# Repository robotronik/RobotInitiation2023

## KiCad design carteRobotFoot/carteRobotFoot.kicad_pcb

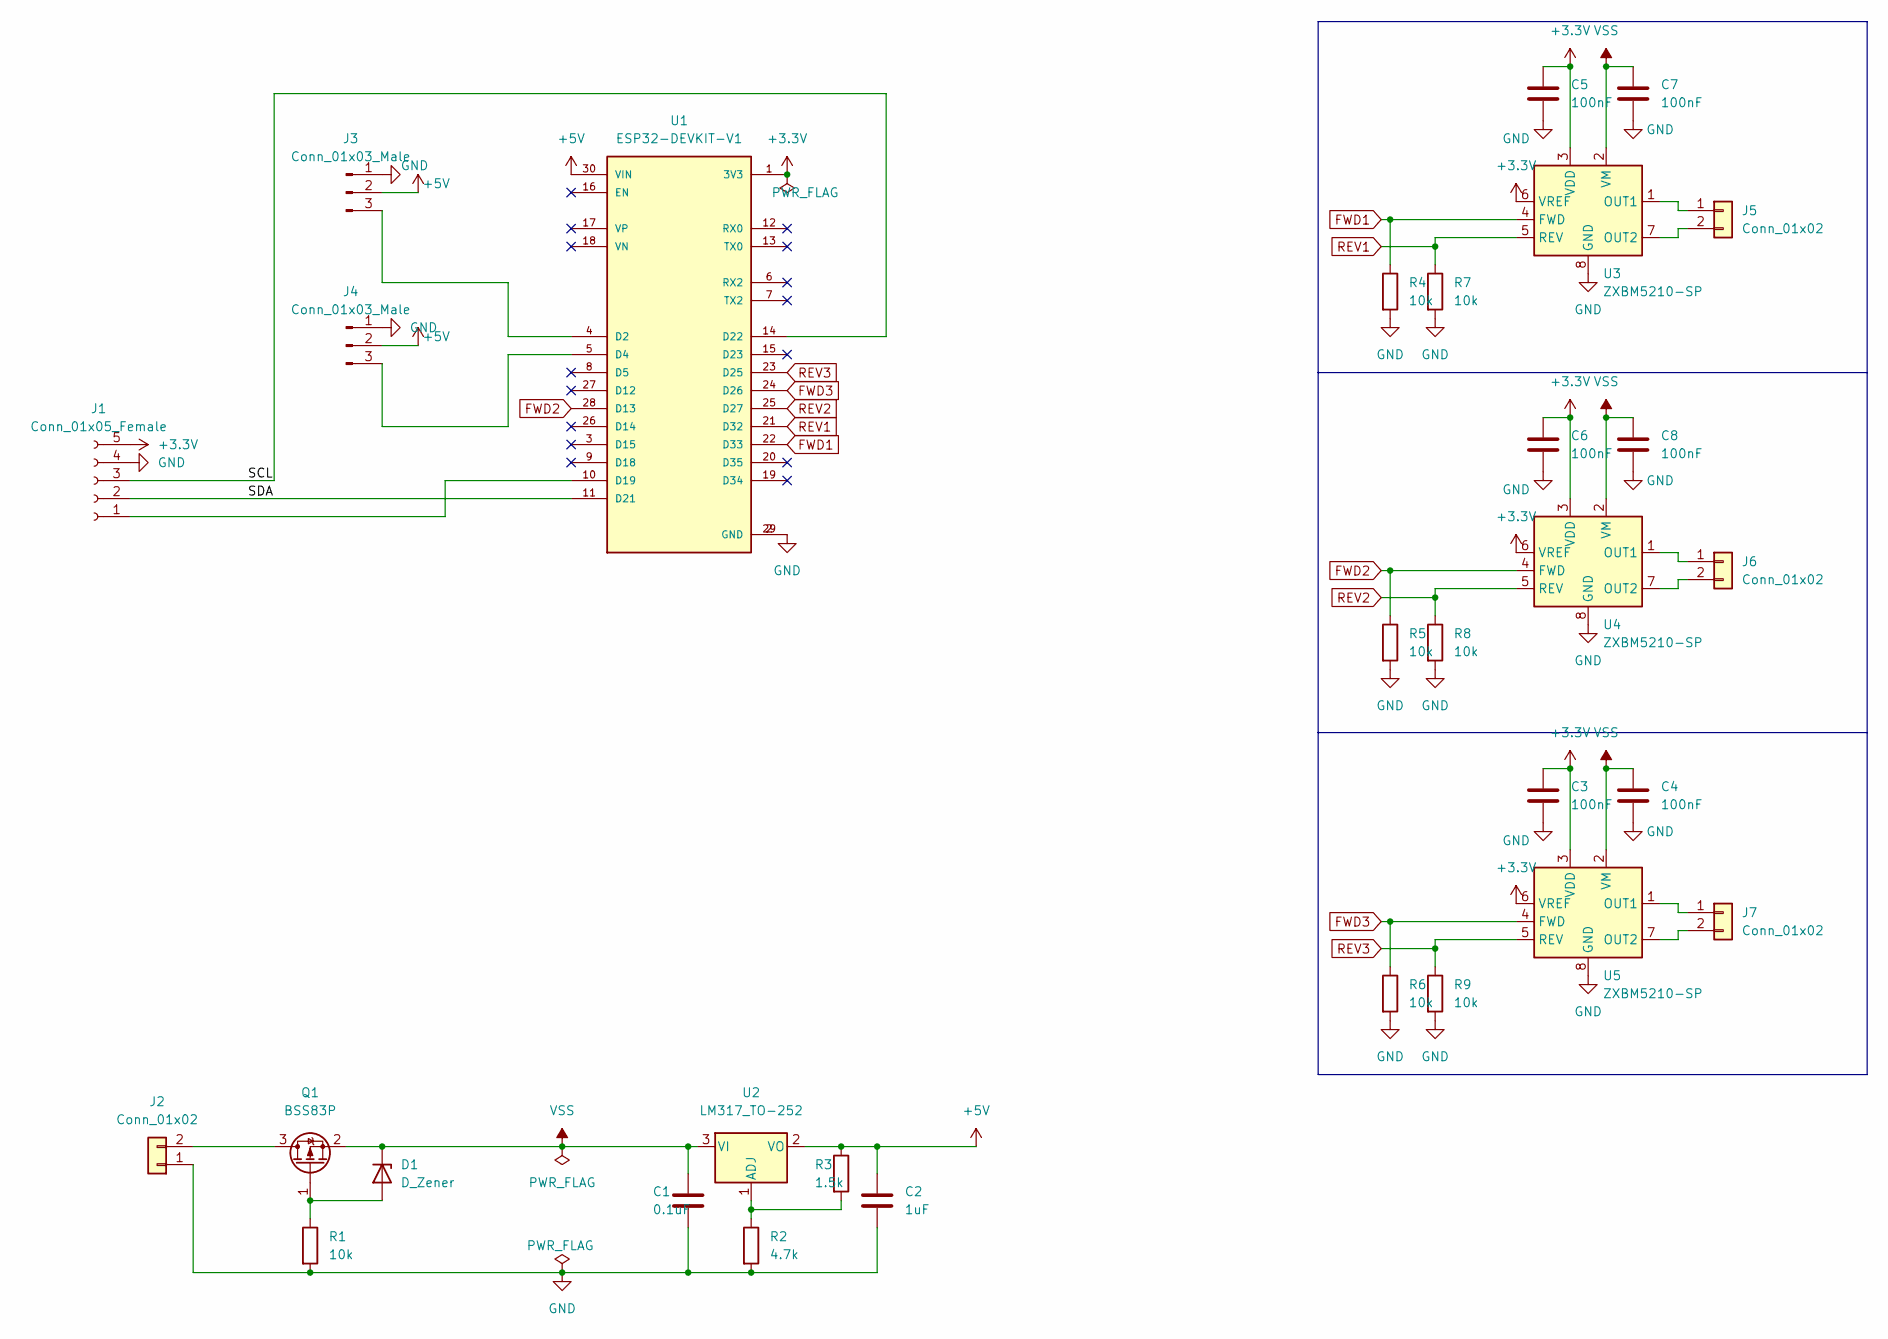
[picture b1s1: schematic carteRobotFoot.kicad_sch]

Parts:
C1: 0.1uF; C_0805_2012Metric
C2: 1uF; C_0805_2012Metric
C3, C4, C5, C6, C7, C8: 100nF; C_0805_2012Metric
D1: D_Zener; D_SOD-123
J1: Conn_01x05_Female; PinHeader_1x05_P2.54mm_Vertical
J2: Conn_01x02; TerminalBlock_bornier-2_P5.08mm
J3, J4: Conn_01x03_Male; PinHeader_1x03_P2.54mm_Vertical
J5, J6, J7: Conn_01x02; JST_XH_B2B-XH-A_1x02_P2.50mm_Vertical
Q1: BSS83P; SOT-23
R1, R4, R5, R6, R7, R8, R9: 10k; R_0805_2012Metric
R2: 4.7k; R_0805_2012Metric
R3: 1.5k; R_0805_2012Metric
U1: ESP32-DEVKIT-V1; MODULE_ESP32_DEVKIT_V1; PARTREV N/A
U2: LM317_TO-252; TO-252-2
U3, U4, U5: ZXBM5210-SP; Diodes_SO-8EP

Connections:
+3.3V: C3.1, C5.1, C6.1, J1.5, U1.1 (3V3), U3.3 (VDD), U3.6 (VREF), U4.3 (VDD), U4.6 (VREF), U5.3 (VDD), U5.6 (VREF)
+5V: C2.1, J3.2, J4.2, R3.1, U1.30 (VIN), U2.2 (VO)
/SCL: J1.3, U1.14 (D22)
/SDA: J1.2, U1.11 (D21)
FWD1: R4.1, U1.22 (D33), U3.4 (FWD)
FWD2: R5.1, U1.28 (D13), U4.4 (FWD)
FWD3: R6.1, U1.24 (D26), U5.4 (FWD)
GND: C1.2, C2.2, C3.2, C4.2, C5.2, C6.2, C7.2, C8.2, J1.4, J2.1, J3.1, J4.1, R1.2, R2.2, R4.2, R5.2, R6.2, R7.2, R8.2, R9.2, U1.2 (GND), U1.29 (GND), U3.8 (GND), U3.9 (GND), U4.8 (GND), U4.9 (GND), U5.8 (GND), U5.9 (GND)
unnamed: D1.2 (A), Q1.1 (G), R1.1
unnamed: J1.1, U1.10 (D19)
unnamed: J2.2, Q1.3 (D)
unnamed: J3.3, U1.4 (D2)
unnamed: J4.3, U1.5 (D4)
unnamed: J5.1, U3.1 (OUT1)
unnamed: J5.2, U3.7 (OUT2)
unnamed: J6.1, U4.1 (OUT1)
unnamed: J6.2, U4.7 (OUT2)
unnamed: J7.1, U5.1 (OUT1)
unnamed: J7.2, U5.7 (OUT2)
unnamed: R2.1, R3.2, U2.1 (ADJ)
REV1: R7.1, U1.21 (D32), U3.5 (REV)
REV2: R8.1, U1.25 (D27), U4.5 (REV)
REV3: R9.1, U1.23 (D25), U5.5 (REV)
VSS: C1.1, C4.1, C7.1, C8.1, D1.1 (K), Q1.2 (S), U2.3 (VI), U3.2 (VM), U4.2 (VM), U5.2 (VM)

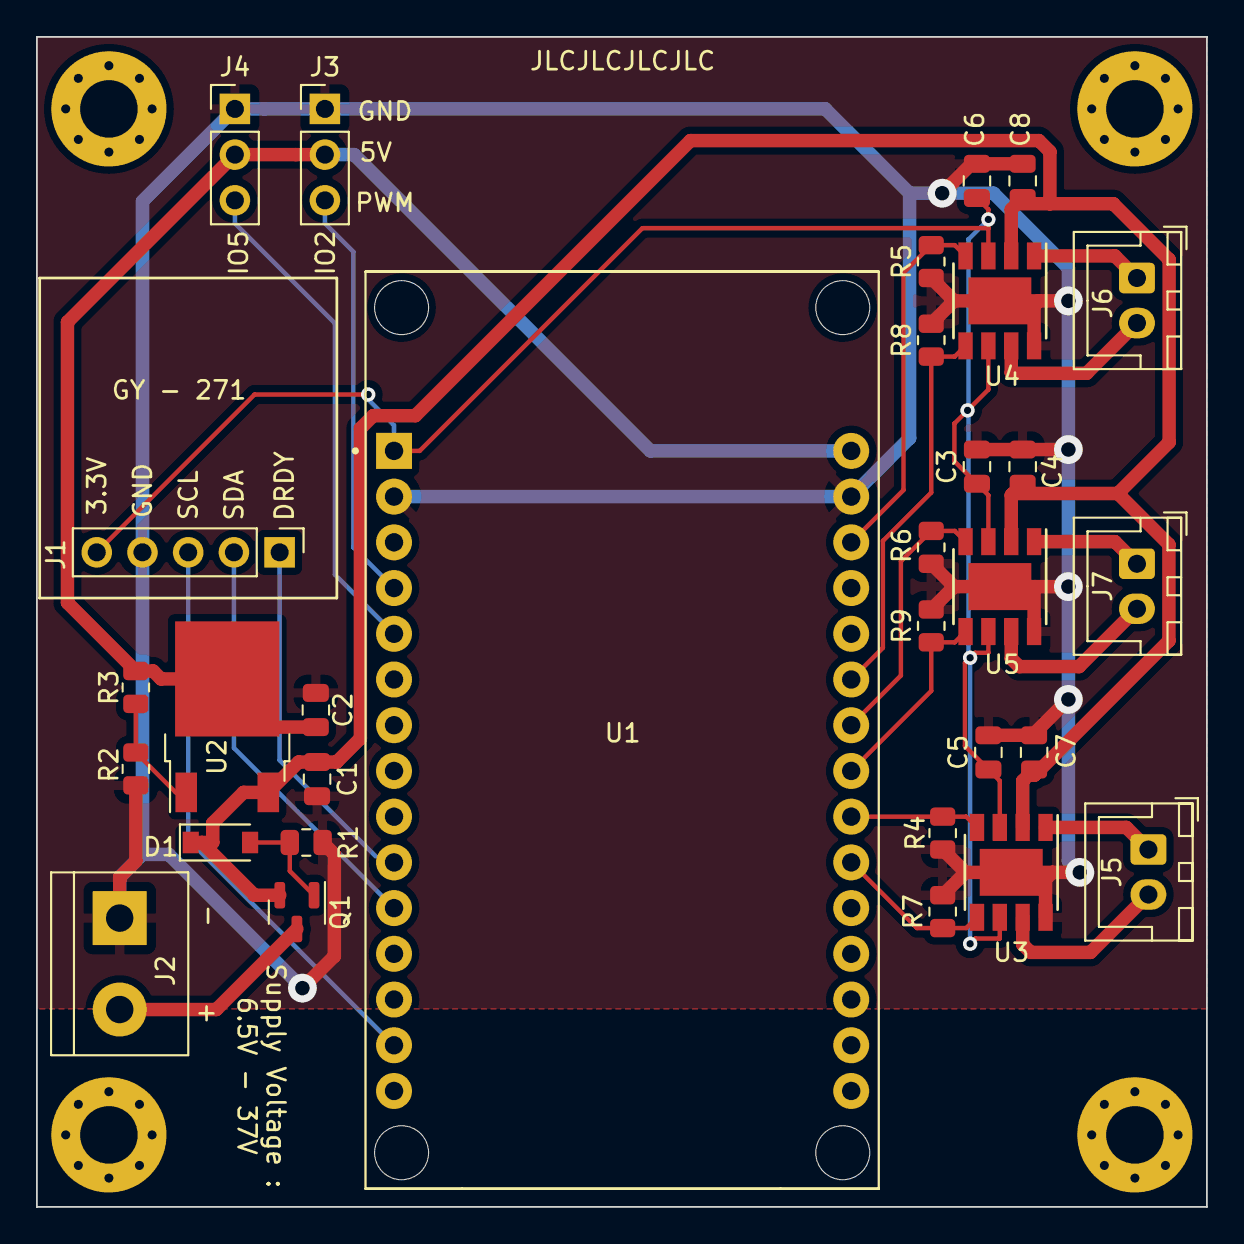
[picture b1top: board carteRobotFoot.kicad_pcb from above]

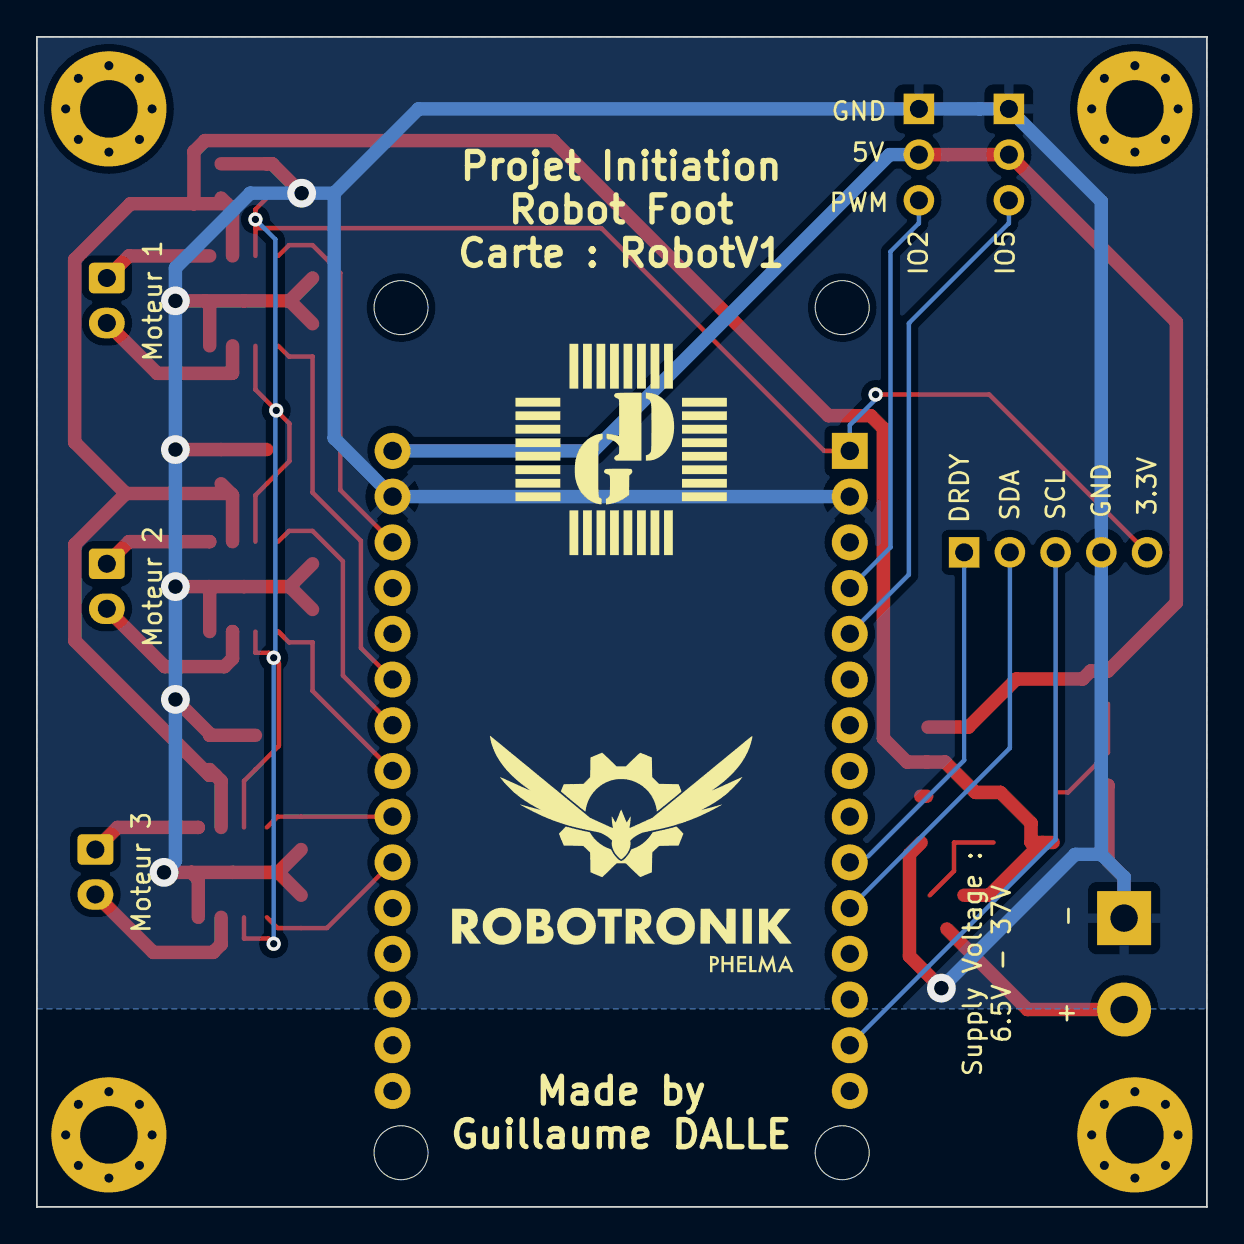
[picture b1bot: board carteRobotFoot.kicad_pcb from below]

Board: 2 copper layers, 65.0 x 65.0 mm, 37 parts (2 on the bottom side), 24 nets.

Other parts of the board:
G1, G2: LOGO
TR1, TR2, TR3, TR4: MountingHole_3.2mm_M3_Pad_Via

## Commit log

2024-06-19 bug fix : passe spiffs to littlfs
